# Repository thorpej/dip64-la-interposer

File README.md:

# A Universal DIP64 Logic Analyzer Interposer Board For Lazy People (like me)
I'm a silly person who likes to hack on old computers, so sometimes I
find myself in need of connecting a large number of logic analyzer
probe leads to a chip in a DIP64 package.  I find this a bit tedious
if my only option is mini-grabbers.  So I built a board to make it
easier!

This work is licensed under the [Creative Commons Attribution
ShareAlike 4.0 International license](https://creativecommons.org/licenses/by-sa/4.0/).

The idea is pretty simple: Downward-facing machined pin headers and
upward-facing machined SIP sockets come together to form an interposer
board that bring the signals out pin headers for the probe leads.  A
Dupont wire is used to jumper the chip's GND pin to any one of the
Common pins, which can then act as ground connections for the probes.
Pointers to GND pins for MC68000 / MC68440 / MC68450 and TMS9900 are
provided for convenience.  Footprints for 0805 SMT decoupling capacitors
are also provided should you find them necessary to counteract the
additional inductance added by the interposer.

If you have any questions about the board, you can reach out to me on
Twitter (*[@thorpej](https://twitter.com/thorpej)*),
BlueSky (*[@thorpej.bsky.social](https://bsky.app/profile/thorpej.bsky.social),
or Mastodon (*[@thorpej@mastodon.sdf.org](https://mastodon.sdf.org/@thorpej)*).

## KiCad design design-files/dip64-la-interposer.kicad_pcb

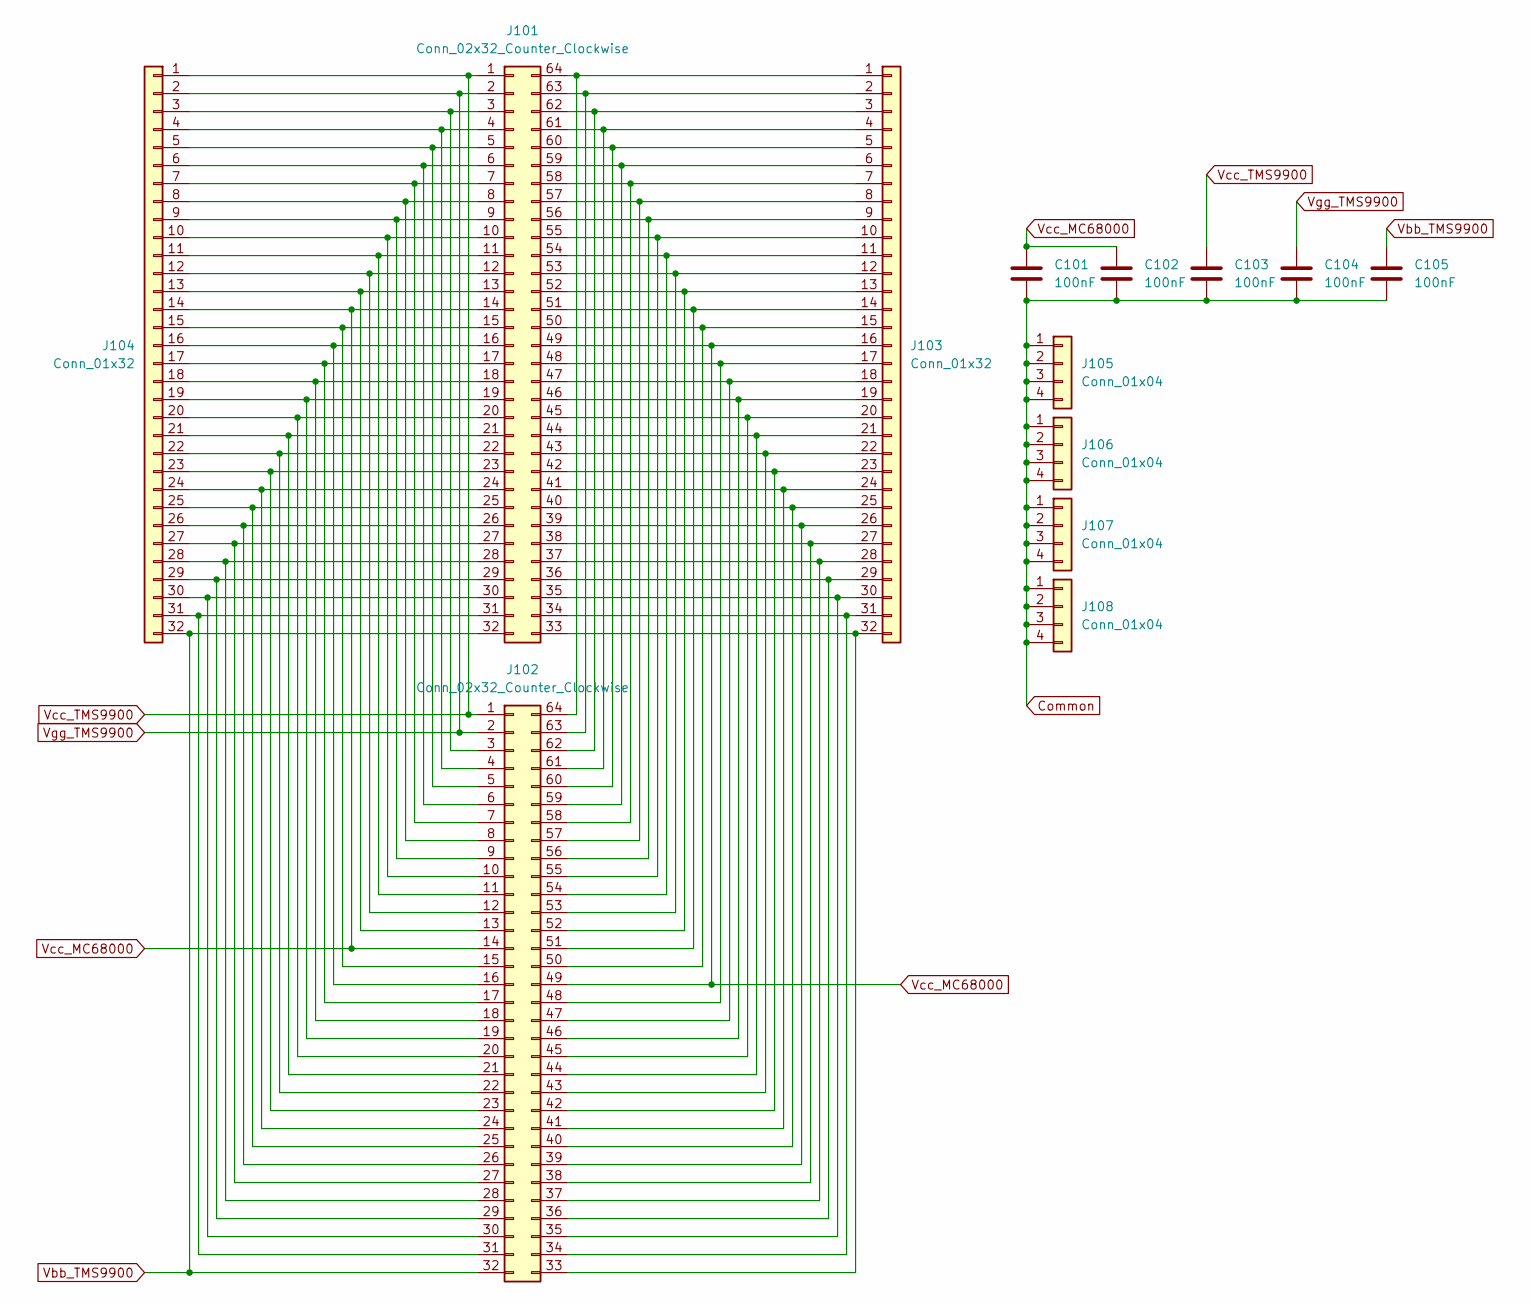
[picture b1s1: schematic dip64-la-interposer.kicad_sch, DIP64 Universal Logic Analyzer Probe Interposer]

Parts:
C101, C102, C103, C104, C105: 100nF; C_0805_2012Metric_Pad1.18x1.45mm_HandSolder
J101, J102: Conn_02x32_Counter_Clockwise; DIP-64_W22.86mm
J103, J104: Conn_01x32; PinHeader_1x32_P2.54mm_Vertical
J105, J106, J107, J108: Conn_01x04; PinHeader_1x04_P2.54mm_Vertical

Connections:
Common: C101.2, C102.2, C103.2, C104.2, C105.2, J105.1, J105.2, J105.3, J105.4, J106.1, J106.2, J106.3, J106.4, J107.1, J107.2, J107.3, J107.4, J108.1, J108.2, J108.3, J108.4
unnamed: J101.3, J102.3, J104.3
unnamed: J101.4, J102.4, J104.4
unnamed: J101.5, J102.5, J104.5
unnamed: J101.6, J102.6, J104.6
unnamed: J101.7, J102.7, J104.7
unnamed: J101.8, J102.8, J104.8
unnamed: J101.9, J102.9, J104.9
unnamed: J101.10, J102.10, J104.10
unnamed: J101.11, J102.11, J104.11
unnamed: J101.12, J102.12, J104.12
unnamed: J101.13, J102.13, J104.13
unnamed: J101.15, J102.15, J104.15
unnamed: J101.16, J102.16, J104.16
unnamed: J101.17, J102.17, J104.17
unnamed: J101.18, J102.18, J104.18
unnamed: J101.19, J102.19, J104.19
unnamed: J101.20, J102.20, J104.20
unnamed: J101.21, J102.21, J104.21
unnamed: J101.22, J102.22, J104.22
unnamed: J101.23, J102.23, J104.23
unnamed: J101.24, J102.24, J104.24
unnamed: J101.25, J102.25, J104.25
unnamed: J101.26, J102.26, J104.26
unnamed: J101.27, J102.27, J104.27
unnamed: J101.28, J102.28, J104.28
unnamed: J101.29, J102.29, J104.29
unnamed: J101.30, J102.30, J104.30
unnamed: J101.31, J102.31, J104.31
unnamed: J101.33, J102.33, J103.32
unnamed: J101.34, J102.34, J103.31
unnamed: J101.35, J102.35, J103.30
unnamed: J101.36, J102.36, J103.29
unnamed: J101.37, J102.37, J103.28
unnamed: J101.38, J102.38, J103.27
unnamed: J101.39, J102.39, J103.26
unnamed: J101.40, J102.40, J103.25
unnamed: J101.41, J102.41, J103.24
unnamed: J101.42, J102.42, J103.23
unnamed: J101.43, J102.43, J103.22
unnamed: J101.44, J102.44, J103.21
unnamed: J101.45, J102.45, J103.20
unnamed: J101.46, J102.46, J103.19
unnamed: J101.47, J102.47, J103.18
unnamed: J101.48, J102.48, J103.17
unnamed: J101.50, J102.50, J103.15
unnamed: J101.51, J102.51, J103.14
unnamed: J101.52, J102.52, J103.13
unnamed: J101.53, J102.53, J103.12
unnamed: J101.54, J102.54, J103.11
unnamed: J101.55, J102.55, J103.10
unnamed: J101.56, J102.56, J103.9
unnamed: J101.57, J102.57, J103.8
unnamed: J101.58, J102.58, J103.7
unnamed: J101.59, J102.59, J103.6
unnamed: J101.60, J102.60, J103.5
unnamed: J101.61, J102.61, J103.4
unnamed: J101.62, J102.62, J103.3
unnamed: J101.63, J102.63, J103.2
unnamed: J101.64, J102.64, J103.1
Vbb_TMS9900: C105.1, J101.32, J102.32, J104.32
Vcc_MC68000: C101.1, C102.1, J101.14, J101.49, J102.14, J102.49, J103.16, J104.14
Vcc_TMS9900: C103.1, J101.1, J102.1, J104.1
Vgg_TMS9900: C104.1, J101.2, J102.2, J104.2

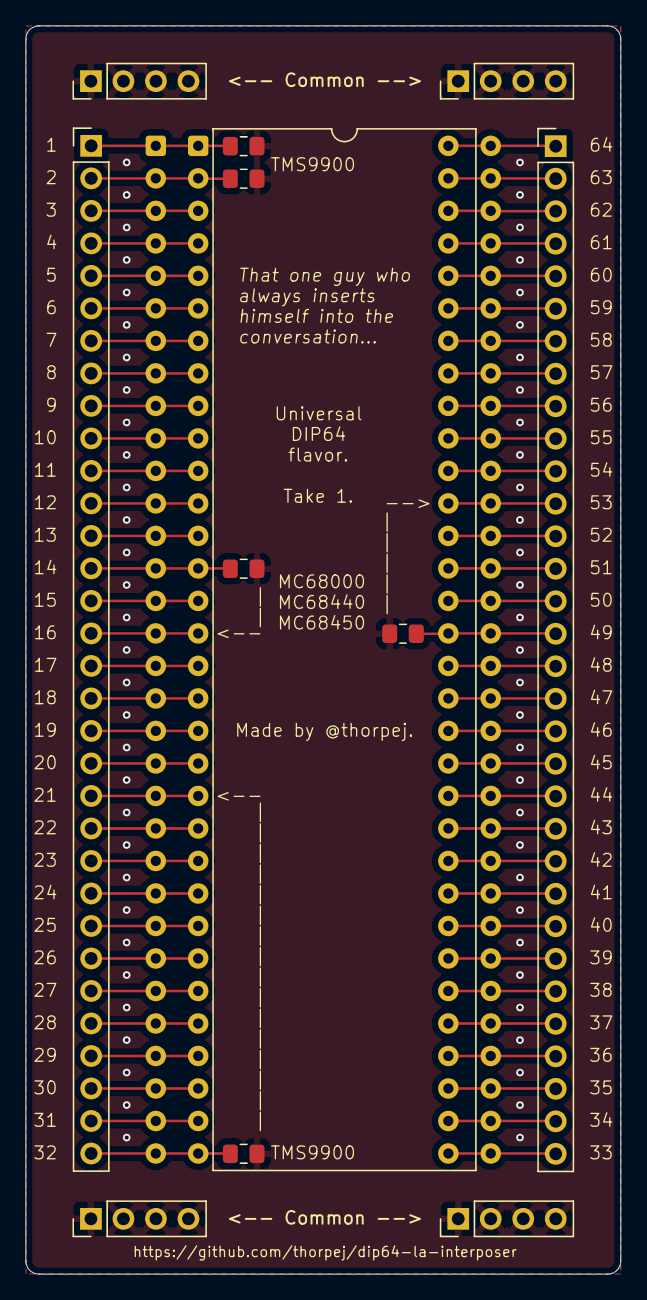
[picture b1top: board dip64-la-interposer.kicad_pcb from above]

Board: 2 copper layers, 46.5 x 97.5 mm, 13 parts (0 on the bottom side), 64 nets.

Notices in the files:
README.md:
CC BY-SA 4.0
design-files/dip64-la-interposer.kicad_pcb:
(c) 2026 Jason R. Thorpe.  See LICENSE.
